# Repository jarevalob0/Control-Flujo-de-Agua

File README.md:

# Descripción
Sistema inteligente capaz de medir, registrar y analizar en tiempo real el consumo de agua en viviendas o instalaciones, controlado desde una aplicación móvil.

# Integrantes
SAMUEL CASALLAS

VICTOR ORTIZ

JUAN AREVALO

GABRIEL ALAMO

DANIEL CAMACHO

# Introducción
El proyecto HydroSense surge ante la creciente necesidad de hacer un uso eficiente del agua, un recurso cada vez más limitado debido al cambio climático, el crecimiento poblacional y la falta de sistemas modernos de monitoreo.

En la mayoría de hogares, el consumo de agua no se mide en tiempo real y las personas no tienen forma de saber cuánta agua gastan en actividades comunes. Esto dificulta la adopción de hábitos responsables y limita la capacidad de detectar fugas o consumos inusuales.

HydroSense busca ofrecer una solución de bajo costo que permita medir el uso del agua de manera precisa, accesible y automática, brindando información útil para reducir el desperdicio y promover la conciencia ambiental.

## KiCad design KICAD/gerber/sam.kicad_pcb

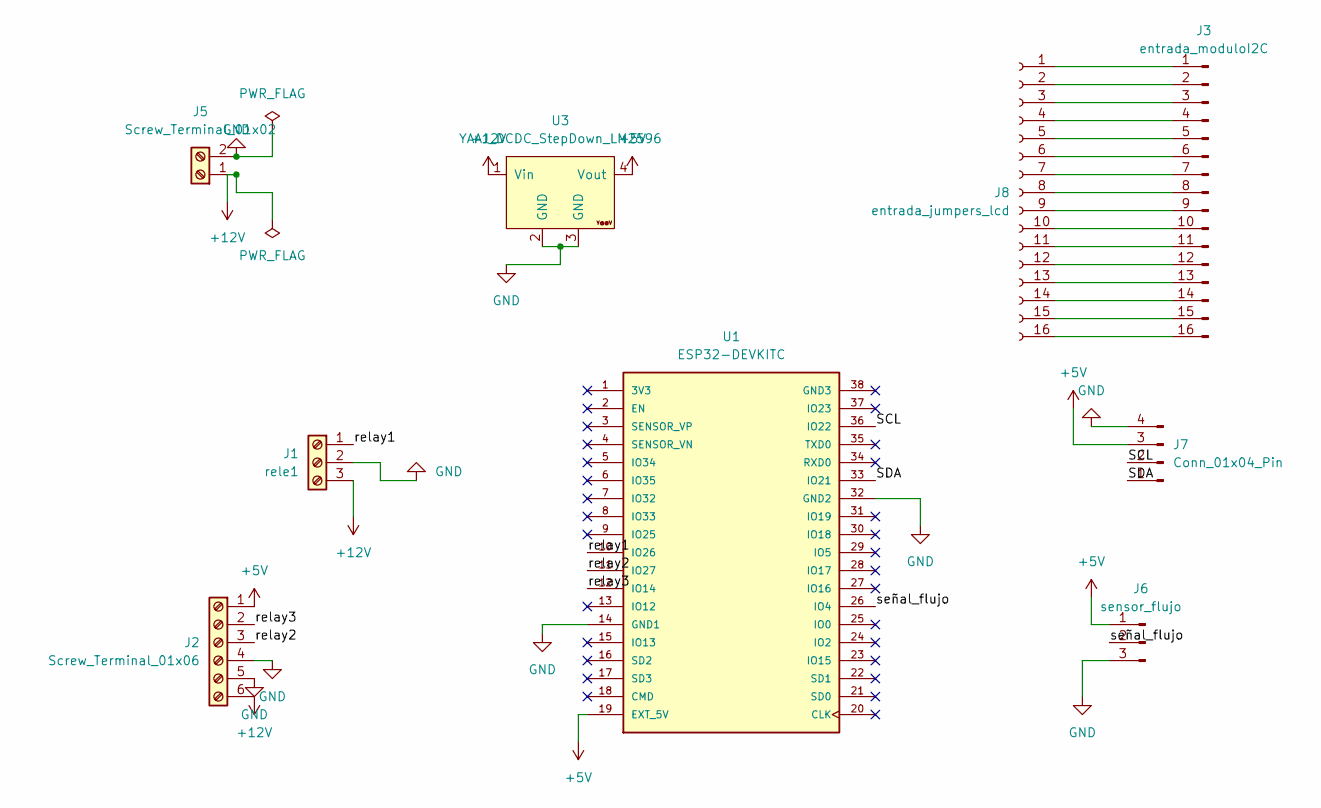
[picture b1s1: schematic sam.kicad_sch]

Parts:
J1: rele1; TerminalBlock_Xinya_XY308-2.54-3P_1x03_P2.54mm_Horizontal
J2: Screw_Terminal_01x06; TerminalBlock_Phoenix_MPT-0,5-6-2.54_1x06_P2.54mm_Horizontal
J3: entrada_moduloI2C; Molex_SL_171971-0016_1x16_P2.54mm_Vertical
J5: Screw_Terminal_01x02; TerminalBlock_Phoenix_MPT-0,5-2-2.54_1x02_P2.54mm_Horizontal
J6: sensor_flujo; PinHeader_1x03_P2.54mm_Vertical
J7: Conn_01x04_Pin; PinSocket_1x04_P2.54mm_Vertical
J8: entrada_jumpers_lcd; PinSocket_1x16_P2.54mm_Vertical
U1: ESP32-DEVKITC; MODULE_ESP32-DEVKITC; PARTREV N/A
U3: YAAJ_DCDC_StepDown_LM2596

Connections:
+5V: J2.1, J6.1, J7.3, U1.19 (EXT_5V), U3.4 (Vout)
+12V: J1.3, J2.6, J5.1, U3.1 (Vin)
/SCL: J7.2, U1.36 (IO22)
/SDA: J7.1, U1.33 (IO21)
/relay1: J1.1, U1.10 (IO26)
/relay2: J2.3, U1.11 (IO27)
/relay3: J2.2, U1.12 (IO14)
/señal_flujo: J6.2, U1.26 (IO4)
GND: J1.2, J2.4, J2.5, J5.2, J6.3, J7.4, U1.14 (GND1), U1.32 (GND2), U3.2 (GND), U3.3 (GND)
unnamed: J3.1, J8.1
unnamed: J3.2, J8.2
unnamed: J3.3, J8.3
unnamed: J3.4, J8.4
unnamed: J3.5, J8.5
unnamed: J3.6, J8.6
unnamed: J3.7, J8.7
unnamed: J3.8, J8.8
unnamed: J3.9, J8.9
unnamed: J3.10, J8.10
unnamed: J3.11, J8.11
unnamed: J3.12, J8.12
unnamed: J3.13, J8.13
unnamed: J3.14, J8.14
unnamed: J3.15, J8.15
unnamed: J3.16, J8.16

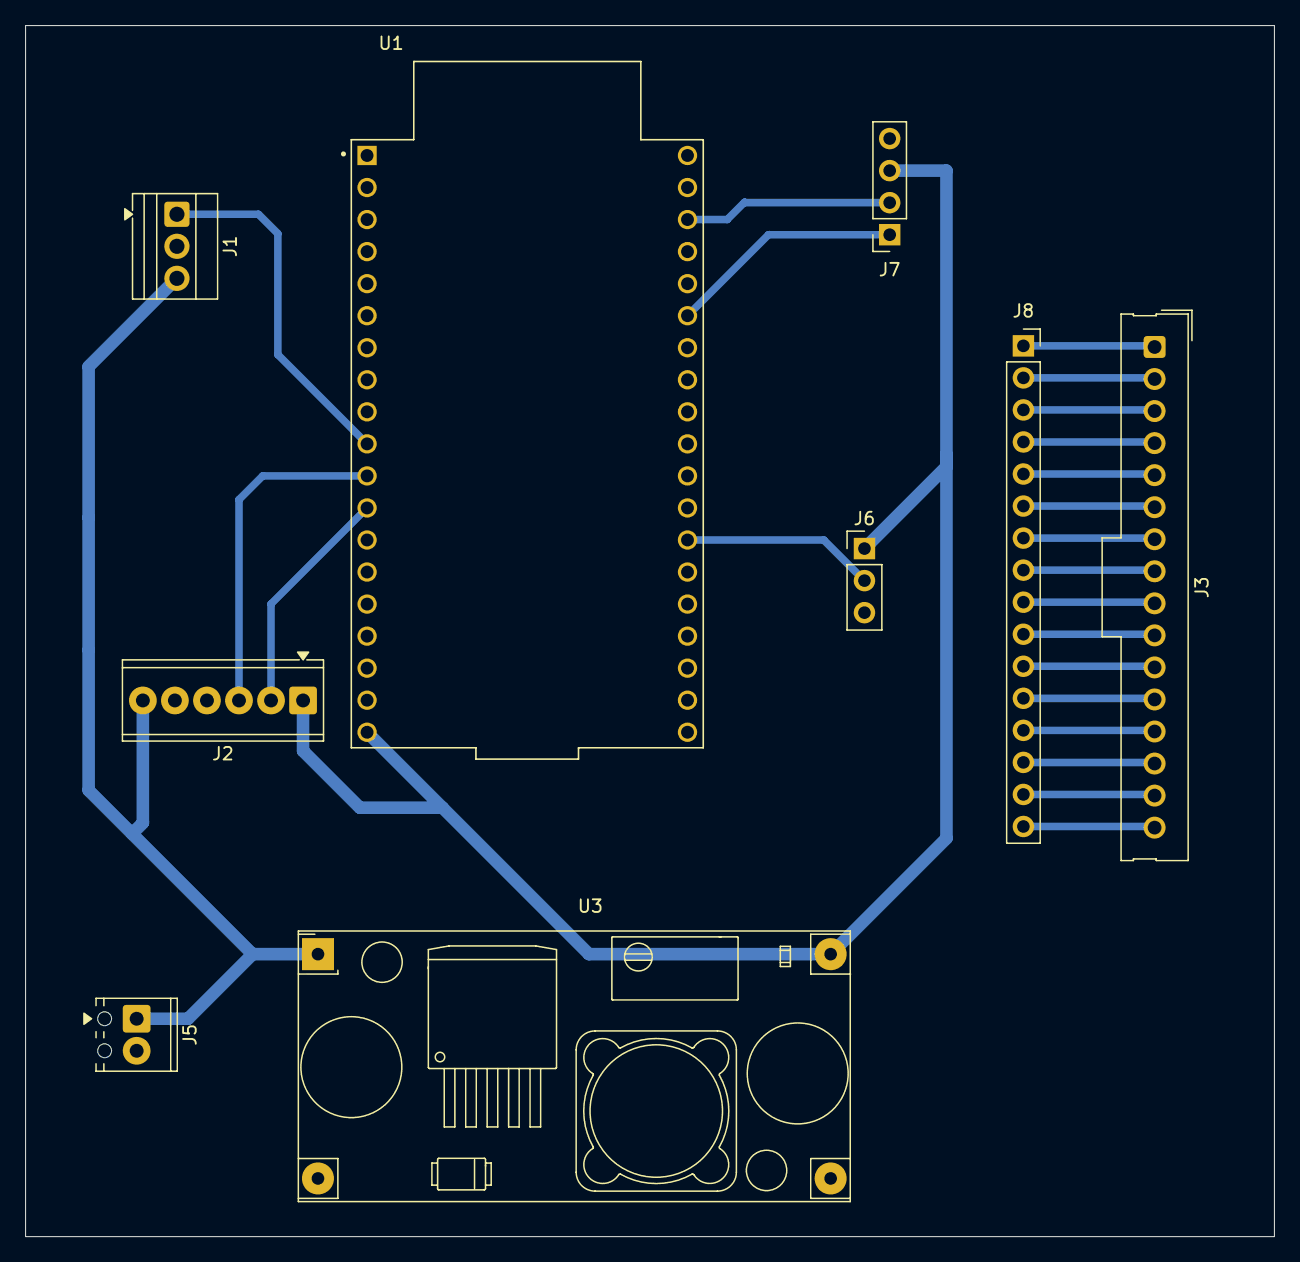
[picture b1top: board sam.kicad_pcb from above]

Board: 2 copper layers, 99.0 x 96.0 mm, 9 parts (0 on the bottom side), 25 nets.

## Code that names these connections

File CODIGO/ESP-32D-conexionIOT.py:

#define BLYNK_TEMPLATE_ID "TMPL2-9qBlvBY"
#define BLYNK_TEMPLATE_NAME "Control de Riego"
#define BLYNK_AUTH_TOKEN "LrsTcscLCbu88JzNmzmm6k4DS6pdao5A"

#include <Wire.h>
#include <WiFi.h>
#include <WiFiClient.h>
#include <BlynkSimpleEsp32.h>
#include <Preferences.h>
#include <LiquidCrystal_I2C.h>

char auth[] = BLYNK_AUTH_TOKEN;
char WIFI[] = "A35";
char PASS[] = "Avlal090";

const uint8_t DATA = 4;
const uint8_t RELAY1 = 14;
const uint8_t RELAY2 = 27;
const uint8_t RELAY3 = 26;

LiquidCrystal_I2C lcd(0x27, 16, 2);

const float PULSES = 7.5;
volatile unsigned int pulse = 0;

float Lpm = 0.0;
float Lps = 0.0;
double total = 0.0;
double waterLimit = 0;
bool limitNotified = false;

unsigned long lastSave = 0;

const int RelayActive = LOW;

#define FLOWLPM V1
#define TOTALL V2
#define VALVE3 V5
#define SOURCE V6
#define LIMIT_SET V11
#define RESET_TOTAL V12

BlynkTimer timer;
Preferences prefs;

void IRAM_ATTR pulseISR() {
  pulse++;
}

void setValve(uint8_t valvePin, bool open) {
  digitalWrite(valvePin, open ? RelayActive : !RelayActive);
}

bool readValveState(uint8_t valvePin) {
  return (digitalRead(valvePin) == RelayActive);
}

BLYNK_WRITE(VALVE3) { setValve(RELAY3, param.asInt() == 1); }

BLYNK_WRITE(LIMIT_SET) {
  waterLimit = param.asDouble();
  prefs.putDouble("limit", waterLimit);
  limitNotified = false;
}

BLYNK_WRITE(RESET_TOTAL) {
  if (param.asInt() == 1) {
    total = 0.0;
    prefs.putDouble("totalL", total);
    Blynk.virtualWrite(TOTALL, total);
    lcd.setCursor(0, 1);
    lcd.print("Tot: 0.0 L     ");
    Serial.println("Total reiniciado desde Blynk");
  }
}
BLYNK_WRITE(SOURCE) {
  int option = param.asInt();

  if (option == 1) {
    setValve(RELAY1, true);
    setValve(RELAY2, false);
  }
  else if (option == 2) {
    setValve(RELAY1, false);
    setValve(RELAY2, true);
  }
}

BLYNK_CONNECTED() {
  Serial.println("Conectado a Blynk!");
  Blynk.syncAll();
  Blynk.virtualWrite(LIMIT_SET, waterLimit);
}

bool leak = false;
bool leakNotified = false;
int leakConfirmCount = 0;
const int LEAK_CONFIRM_THRESHOLD = 2;
int leakClearCount = 0;
const int LEAK_CLEAR_THRESHOLD = 2;

void measureAndPublish() {
  noInterrupts();
  unsigned int pulses = pulse;
  pulse = 0;
  interrupts();

  Lpm = ((float)pulses) / PULSES;
  Lps = Lpm / 60.0;
  total += Lps;

  if (waterLimit > 0 && total >= waterLimit && !limitNotified) {
    limitNotified = true;
    Blynk.logEvent("limite_agua", "Se superó el límite de consumo configurado");
    lcd.clear();
    lcd.setCursor(0, 0);
    lcd.print("LIMITE SUPERADO");
  }

  bool v3 = readValveState(RELAY3);

  if (Lps > 0.01 && !v3) {  
    leakConfirmCount++;
    leakClearCount = 0;
    if (leakConfirmCount >= LEAK_CONFIRM_THRESHOLD) leak = true;
} 
else {
    leakClearCount++;
    leakConfirmCount = 0;
    if (leakClearCount >= LEAK_CLEAR_THRESHOLD) leak = false;
}

  if (leak && !leakNotified) {
    leakNotified = true;
    Blynk.logEvent("alerta_de_fuga", "Alerta: Posible fuga detectada");
  } else if (!leak && leakNotified) {
    leakNotified = false;
    Blynk.logEvent("alerta_de_fuga", "La fuga ha cesado");
  }

  Blynk.virtualWrite(FLOWLPM, Lpm);
  Blynk.virtualWrite(TOTALL, total);

  lcd.setCursor(0, 0);
  lcd.print("Flow:");
  lcd.print(Lpm, 2);
  lcd.print(" L/m   ");
  lcd.setCursor(0, 1);
  lcd.print("Tot:");
  lcd.print(total, 1);
  lcd.print(" L    ");
}

void saveState() {
  unsigned long now = millis();
  if (now - lastSave >= 60000UL) {
    lastSave = now;
    prefs.putDouble("totalL", total);
  }
}

void setup() {
  Serial.begin(115200);
  delay(200);

  pinMode(DATA, INPUT_PULLUP);
  attachInterrupt(digitalPinToInterrupt(DATA), pulseISR, RISING);

  pinMode(RELAY1, OUTPUT);
  pinMode(RELAY2, OUTPUT);
  pinMode(RELAY3, OUTPUT);
  digitalWrite(RELAY1, !RelayActive);
  digitalWrite(RELAY2, !RelayActive);
  digitalWrite(RELAY3, !RelayActive);

  Wire.begin(21, 22);
  lcd.init();
  lcd.backlight();
  lcd.setCursor(0, 0);
  lcd.print("Iniciando...");
  lcd.setCursor(0, 1);
  lcd.print("ESP32 Riego");

  prefs.begin("waterProj", false);
  total = prefs.getDouble("totalL", 0.0);
  waterLimit = prefs.getDouble("limit", 0.0);

  lcd.clear();
  lcd.setCursor(0, 0);
  lcd.print("Conectando WiFi");

  WiFi.begin(WIFI, PASS);
  unsigned long start = millis();
  while (WiFi.status() != WL_CONNECTED && millis() - start < 15000) {
    delay(300);
    Serial.print(".");
  }

  lcd.clear();
  if (WiFi.status() == WL_CONNECTED) lcd.print("WiFi OK");
  else lcd.print("Sin WiFi");

  WiFi.mode(WIFI_STA);

  Blynk.config(auth);
  Blynk.connect();

  timer.setInterval(1000, measureAndPublish);
  timer.setInterval(60000, saveState);

  delay(1000);
  lcd.clear();
}

void loop() {
  if (WiFi.status() != WL_CONNECTED) WiFi.begin(WIFI, PASS);
  if (!Blynk.connected()) Blynk.connect(500);

  Blynk.run();
  timer.run();
}

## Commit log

2025-12-03 Create CRONOGRAMA
2025-12-03 Create CODIGO-ESP32D
2025-12-03 Create DIAGRAMAS
2025-12-03 Create DISEÑOS
2025-12-03 Create KICAD
2025-12-03 Create POSTER
2025-12-03 Create EVIDENCIAS
2025-12-03 Create Informes
2025-12-03 Rename DIAGRAMAS to Diagramas
2025-12-03 Create a
2025-12-03 Rename diagramacaja.drawio.png to DiagramaDeCaja.png
2025-12-10 Create Jj
2025-12-10 Create Prueba relés
2025-12-10 Create prueba sensor flujo
2025-12-10 Create prueba pantalla LCD
2025-12-12 Create jgg
2025-12-12 Create ESP-32D
2025-12-12 Rename ESP-32D to ESP-32D.py
2025-12-12 Create jfi
2025-12-12 Create hdjoshf
2025-12-13 Rename ESP-32D.py to ESP-32D-conexionIOT.py
